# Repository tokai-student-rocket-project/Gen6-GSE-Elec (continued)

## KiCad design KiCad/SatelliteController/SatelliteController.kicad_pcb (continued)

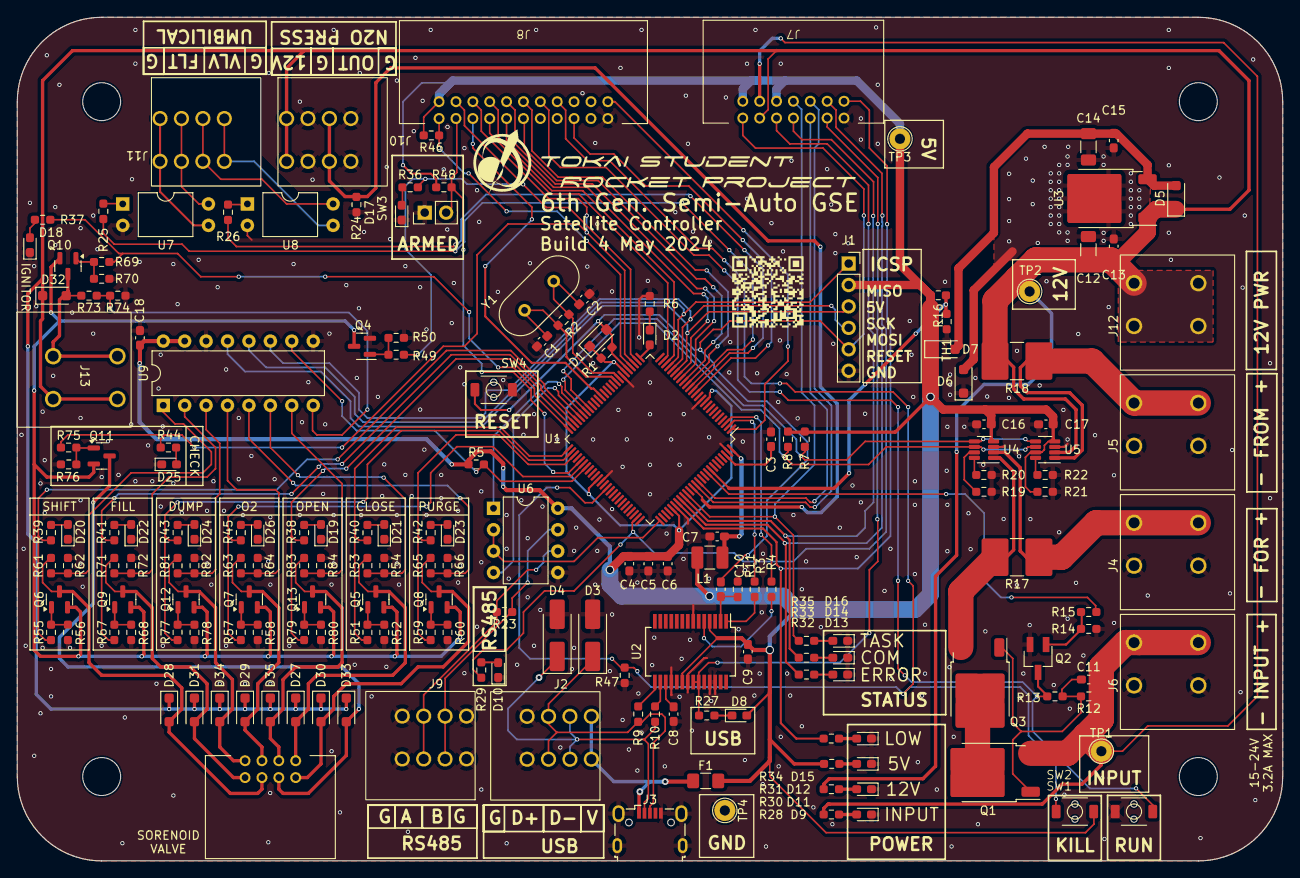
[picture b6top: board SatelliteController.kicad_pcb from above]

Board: 2 copper layers, 150.0 x 100.0 mm, 185 parts (0 on the bottom side), 133 nets.

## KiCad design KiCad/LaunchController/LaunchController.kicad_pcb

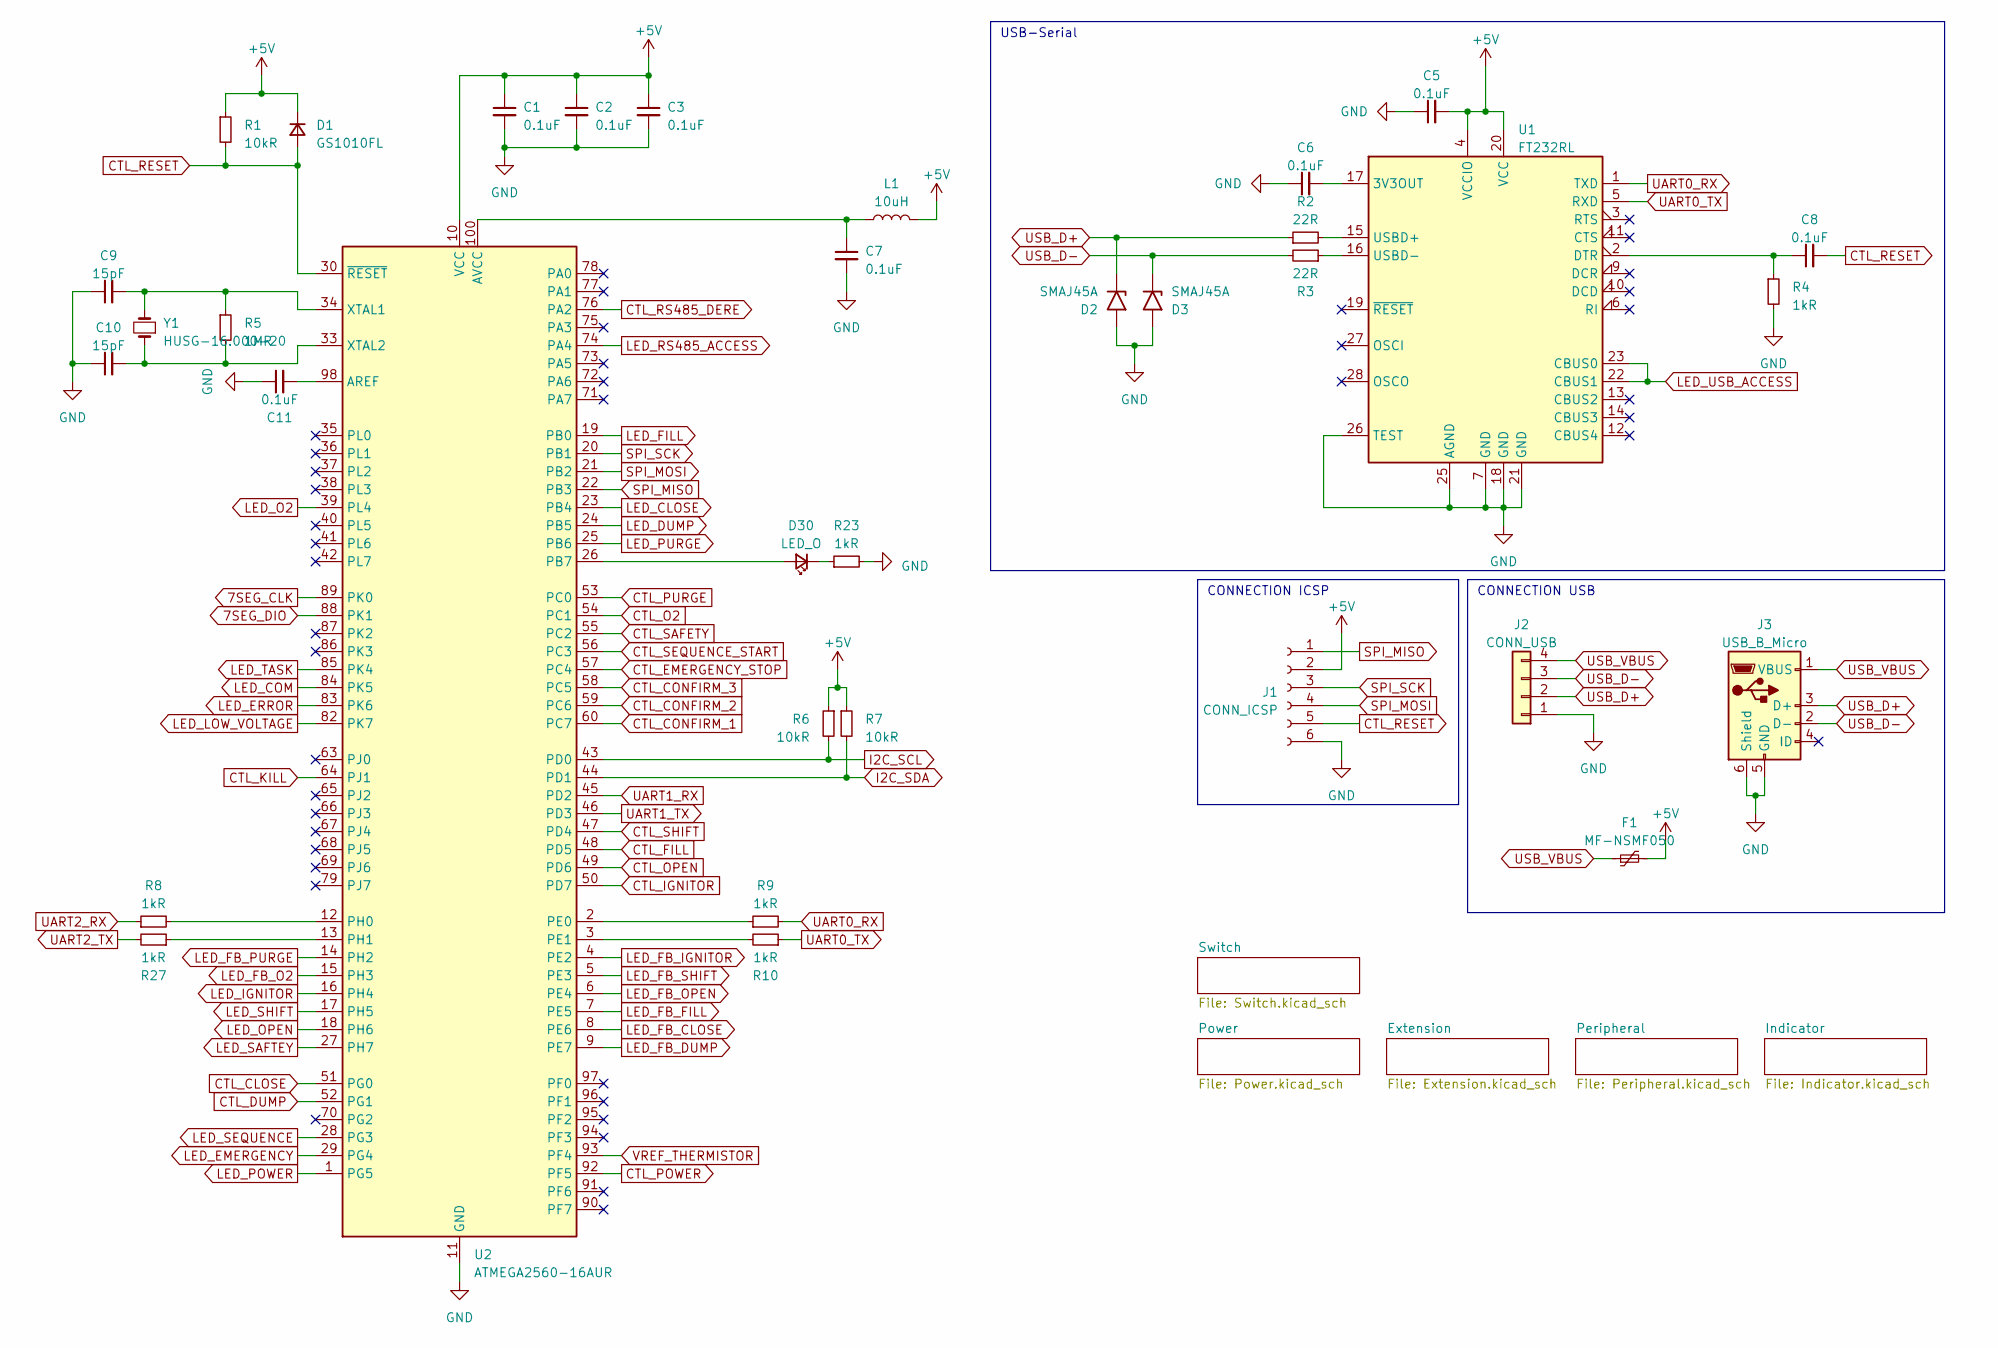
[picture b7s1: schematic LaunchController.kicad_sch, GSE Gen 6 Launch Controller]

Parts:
C1, C2, C3, C5, C6, C7, C8, C11: 0.1uF; C_0603_1608Metric_Pad1.08x0.95mm_HandSolder
C9, C10: 15pF; C_0603_1608Metric_Pad1.08x0.95mm_HandSolder
D1: GS1010FL; D_SOD-123F
D2, D3: SMAJ45A; D_SMA_Handsoldering
D30: LED_O; LED_0603_1608Metric_Pad1.05x0.95mm_HandSolder
F1: MF-NSMF050; Fuse_1206_3216Metric_Pad1.42x1.75mm_HandSolder
J1: CONN_ICSP; PinSocket_1x06_P2.54mm_Vertical
J2: CONN_USB; TB401-1-4-E
J3: USB_B_Micro; USB_Micro-B_Wuerth_629105150521
L1: 10uH; L_1210_3225Metric_Pad1.42x2.65mm_HandSolder
R1, R6, R7: 10kR; R_0603_1608Metric_Pad0.98x0.95mm_HandSolder
R2, R3: 22R; R_0603_1608Metric_Pad0.98x0.95mm_HandSolder
R4, R8, R9, R10, R23, R27: 1kR; R_0603_1608Metric_Pad0.98x0.95mm_HandSolder
R5: 1MR; R_0603_1608Metric_Pad0.98x0.95mm_HandSolder
U1: FT232RL; SSOP-28_5.3x10.2mm_P0.65mm
U2: ATMEGA2560-16AUR; TQFP-100_14x14mm_P0.5mm
Y1: HUSG-16.000-20; Crystal_HC49-U_Vertical

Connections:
7SEG_CLK: U2.89 (PK0); also elsewhere on the board
7SEG_DIO: U2.88 (PK1); also elsewhere on the board
CONN_LED_5V: C1.1, C2.1, C3.1, C5.2, D1.1 (K), F1.2, J1.2, L1.2, R1.1, R6.1, R7.1, U1.4 (VCCIO), U1.20 (VCC), U2.10 (VCC), U2.31 (VCC), U2.61 (VCC), U2.80 (VCC); also elsewhere on the board
CONN_LED_CLOSE: U2.23 (PB4); also elsewhere on the board
CONN_LED_COM: U2.84 (PK5); also elsewhere on the board
CONN_LED_DUMP: U2.24 (PB5); also elsewhere on the board
CONN_LED_EMERGENCY: U2.29 (PG4); also elsewhere on the board
CONN_LED_ERROR: U2.83 (PK6); also elsewhere on the board
CONN_LED_FILL: U2.19 (PB0); also elsewhere on the board
CONN_LED_IGNITOR: U2.16 (PH4); also elsewhere on the board
CONN_LED_LOW_VOLTAGE: U2.82 (PK7); also elsewhere on the board
CONN_LED_O2: U2.39 (PL4); also elsewhere on the board
CONN_LED_OPEN: U2.18 (PH6); also elsewhere on the board
CONN_LED_PURGE: U2.25 (PB6); also elsewhere on the board
CONN_LED_RS485_ACCESS: U2.74 (PA4); also elsewhere on the board
CONN_LED_SAFTEY: U2.27 (PH7); also elsewhere on the board
CONN_LED_SEQUENCE: U2.28 (PG3); also elsewhere on the board
CONN_LED_SHIFT: U2.17 (PH5); also elsewhere on the board
CONN_LED_TASK: U2.85 (PK4); also elsewhere on the board
CONN_LED_USB_ACCESS: U1.22 (CBUS1), U1.23 (CBUS0); also elsewhere on the board
CTL_CLOSE: U2.51 (PG0); also elsewhere on the board
CTL_CONFIRM_1: U2.60 (PC7); also elsewhere on the board
CTL_CONFIRM_2: U2.59 (PC6); also elsewhere on the board
CTL_CONFIRM_3: U2.58 (PC5); also elsewhere on the board
CTL_DUMP: U2.52 (PG1); also elsewhere on the board
CTL_EMERGENCY_STOP: U2.57 (PC4); also elsewhere on the board
CTL_FILL: U2.48 (PD5); also elsewhere on the board
CTL_IGNITOR: U2.50 (PD7); also elsewhere on the board
CTL_KILL: U2.64 (PJ1); also elsewhere on the board
CTL_O2: U2.54 (PC1); also elsewhere on the board
CTL_OPEN: U2.49 (PD6); also elsewhere on the board
CTL_POWER: U2.92 (PF5); also elsewhere on the board
CTL_PURGE: U2.53 (PC0); also elsewhere on the board
CTL_RESET: C8.2, D1.2 (A), J1.5, R1.2, U2.30 (~RESET); also elsewhere on the board
CTL_RS485_DERE: U2.76 (PA2); also elsewhere on the board
CTL_SAFETY: U2.55 (PC2); also elsewhere on the board
CTL_SEQUENCE_START: U2.56 (PC3); also elsewhere on the board
CTL_SHIFT: U2.47 (PD4); also elsewhere on the board
GND: C1.2, C2.2, C3.2, C5.1, C6.1, C7.2, C9.1, C10.1, C11.1, D2.2 (A2), D3.2 (A2), J1.6, J2.1, J3.5 (GND), J3.6 (Shield), R4.2, R23.2, U1.7 (GND), U1.18 (GND), U1.21 (GND), U1.25 (AGND), U1.26 (TEST), U2.11 (GND), U2.32 (GND), U2.62 (GND), U2.81 (GND), U2.99 (GND); also elsewhere on the board
I2C_SCL: R6.2, U2.43 (PD0); also elsewhere on the board
I2C_SDA: R7.2, U2.44 (PD1); also elsewhere on the board
unnamed: D30.2 (A), U2.26 (PB7)
unnamed: D30.1 (K), R23.1
unnamed: C6.2, U1.17 (3V3OUT)
unnamed: C8.1, R4.1, U1.2 (DTR)
unnamed: R2.2, U1.15 (USBD+)
unnamed: R3.1, U1.16 (USBD-)
unnamed: C11.2, U2.98 (AREF)
unnamed: C7.1, L1.1, U2.100 (AVCC)
unnamed: R9.1, U2.2 (PE0)
unnamed: R10.2, U2.3 (PE1)
unnamed: R8.2, U2.12 (PH0)
unnamed: R27.1, U2.13 (PH1)
unnamed: C9.2, R5.1, U2.34 (XTAL1), Y1.2
unnamed: C10.2, R5.2, U2.33 (XTAL2), Y1.1
SPI_MISO: J1.1, U2.22 (PB3)
SPI_MOSI: J1.4, U2.21 (PB2)
SPI_SCK: J1.3, U2.20 (PB1)
UART0_RX: R9.2, U1.1 (TXD)
UART0_TX: R10.1, U1.5 (RXD)
UART1_RX: U2.45 (PD2); also elsewhere on the board
UART1_TX: U2.46 (PD3); also elsewhere on the board
UART2_RX: R8.1; also elsewhere on the board
UART2_TX: R27.2; also elsewhere on the board
USB_D+: D2.1 (A1), J2.2, J3.3 (D+), R2.1
USB_D-: D3.1 (A1), J2.3, J3.2 (D-), R3.2
USB_VBUS: F1.1, J2.4, J3.1 (VBUS)
VREF_THERMISTOR: U2.93 (PF4); also elsewhere on the board

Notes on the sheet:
CONNECTION ICSP
CONNECTION USB
USB-Serial

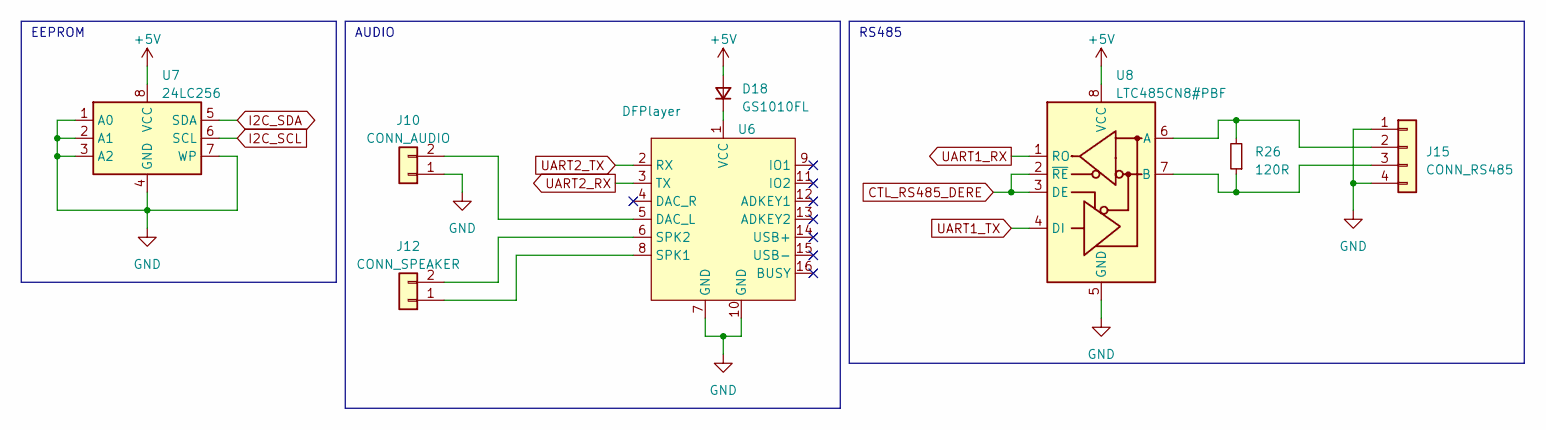
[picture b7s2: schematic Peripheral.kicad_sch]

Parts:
D18: GS1010FL; D_SOD-123F
J10: CONN_AUDIO; TB401-1-2-E
J12: CONN_SPEAKER; TB401-1-2-E
J15: CONN_RS485; TB401-1-4-E
R26: 120R; R_0603_1608Metric_Pad0.98x0.95mm_HandSolder
U6: DFPlayer; DFPlayer-mini
U7: 24LC256; DIP-8_W7.62mm
U8: LTC485CN8#PBF; DIP-8_W7.62mm

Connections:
CONN_LED_5V: D18.2 (A), U7.8 (VCC), U8.8 (VCC); also elsewhere on the board
CTL_RS485_DERE: U8.2 (~RE), U8.3 (DE); also elsewhere on the board
GND: J10.1, J15.1, J15.4, U6.7 (GND), U6.10 (GND), U7.1 (A0), U7.2 (A1), U7.3 (A2), U7.4 (GND), U7.7 (WP), U8.5 (GND); also elsewhere on the board
I2C_SCL: U7.6 (SCL); also elsewhere on the board
I2C_SDA: U7.5 (SDA); also elsewhere on the board
unnamed: D18.1 (K), U6.1 (VCC)
unnamed: J10.2, U6.5 (DAC_L)
unnamed: J12.1, U6.8 (SPK1)
unnamed: J12.2, U6.6 (SPK2)
unnamed: J15.2, R26.2, U8.6 (A)
unnamed: J15.3, R26.1, U8.7 (B)
UART1_RX: U8.1 (RO); also elsewhere on the board
UART1_TX: U8.4 (DI); also elsewhere on the board
UART2_RX: U6.3 (TX); also elsewhere on the board
UART2_TX: U6.2 (RX); also elsewhere on the board

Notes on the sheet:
AUDIO
EEPROM
RS485

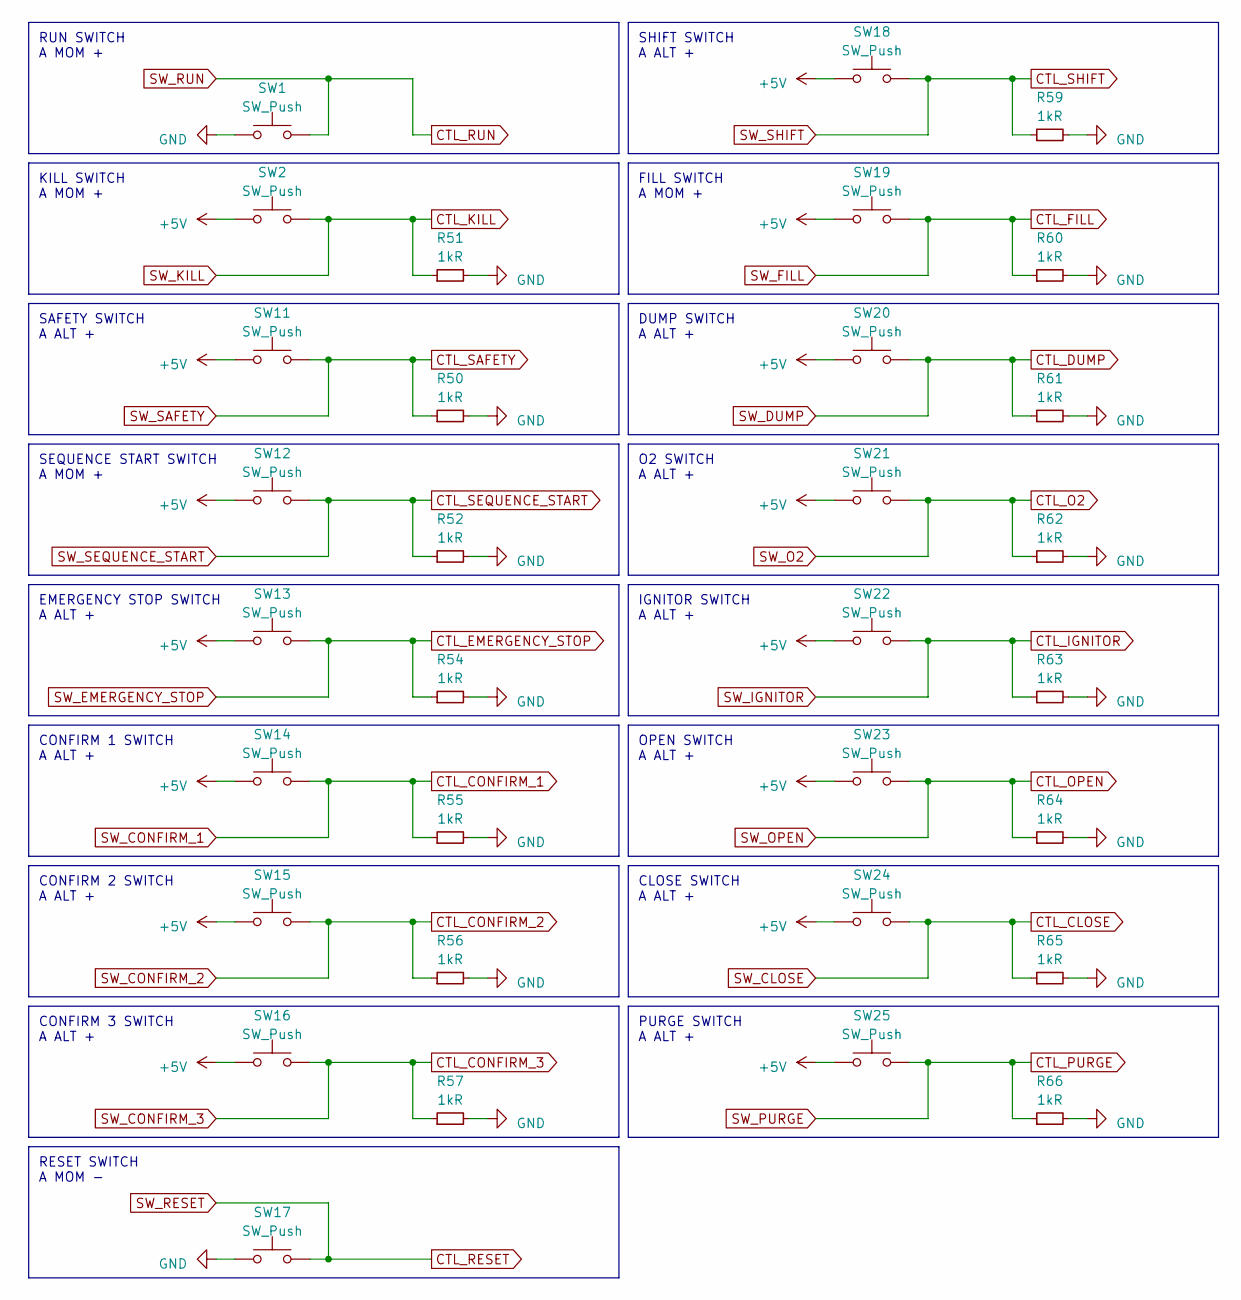
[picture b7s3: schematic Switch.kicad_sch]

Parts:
R50, R51, R52, R54, R55, R56, R57, R59, R60, R61, R62, R63, R64, R65, R66: 1kR; R_0603_1608Metric_Pad0.98x0.95mm_HandSolder
SW1, SW2, SW17: SW_Push; TVAF06-A020B-R
SW11, SW12, SW13, SW14, SW15, SW16, SW18, SW19, SW20, SW21, SW22, SW23, SW24, SW25: SW_Push; PinHeader_1x02_P2.54mm_Vertical

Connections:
CONN_LED_5V: SW2.1, SW11.1, SW12.1, SW13.1, SW14.1, SW15.1, SW16.1, SW18.1, SW19.1, SW20.1, SW21.1, SW22.1, SW23.1, SW24.1, SW25.1; also elsewhere on the board
CTL_CLOSE: R65.1, SW24.2; also elsewhere on the board
CTL_CONFIRM_1: R55.1, SW14.2; also elsewhere on the board
CTL_CONFIRM_2: R56.1, SW15.2; also elsewhere on the board
CTL_CONFIRM_3: R57.1, SW16.2; also elsewhere on the board
CTL_DUMP: R61.1, SW20.2; also elsewhere on the board
CTL_EMERGENCY_STOP: R54.1, SW13.2; also elsewhere on the board
CTL_FILL: R60.1, SW19.2; also elsewhere on the board
CTL_IGNITOR: R63.1, SW22.2; also elsewhere on the board
CTL_KILL: R51.1, SW2.2; also elsewhere on the board
CTL_O2: R62.1, SW21.2; also elsewhere on the board
CTL_OPEN: R64.1, SW23.2; also elsewhere on the board
CTL_PURGE: R66.1, SW25.2; also elsewhere on the board
CTL_RESET: SW17.2; also elsewhere on the board
CTL_RUN: SW1.2; also elsewhere on the board
CTL_SAFETY: R50.1, SW11.2; also elsewhere on the board
CTL_SEQUENCE_START: R52.1, SW12.2; also elsewhere on the board
CTL_SHIFT: R59.1, SW18.2; also elsewhere on the board
GND: R50.2, R51.2, R52.2, R54.2, R55.2, R56.2, R57.2, R59.2, R60.2, R61.2, R62.2, R63.2, R64.2, R65.2, R66.2, SW1.1, SW17.1; also elsewhere on the board

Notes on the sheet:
SEQUENCE START SWITCH A MOM +
OPEN SWITCH A ALT +
CONFIRM 1 SWITCH A ALT +
IGNITOR SWITCH A ALT +
KILL SWITCH A MOM +
CLOSE SWITCH A ALT +
CONFIRM 2 SWITCH A ALT +
SAFETY SWITCH A ALT +
PURGE SWITCH A ALT +
CONFIRM 3 SWITCH A ALT +
SHIFT SWITCH A ALT +
RESET SWITCH A MOM -
FILL SWITCH A MOM +
RUN SWITCH A MOM +
DUMP SWITCH A ALT +
EMERGENCY STOP SWITCH A ALT +
O2 SWITCH A ALT +

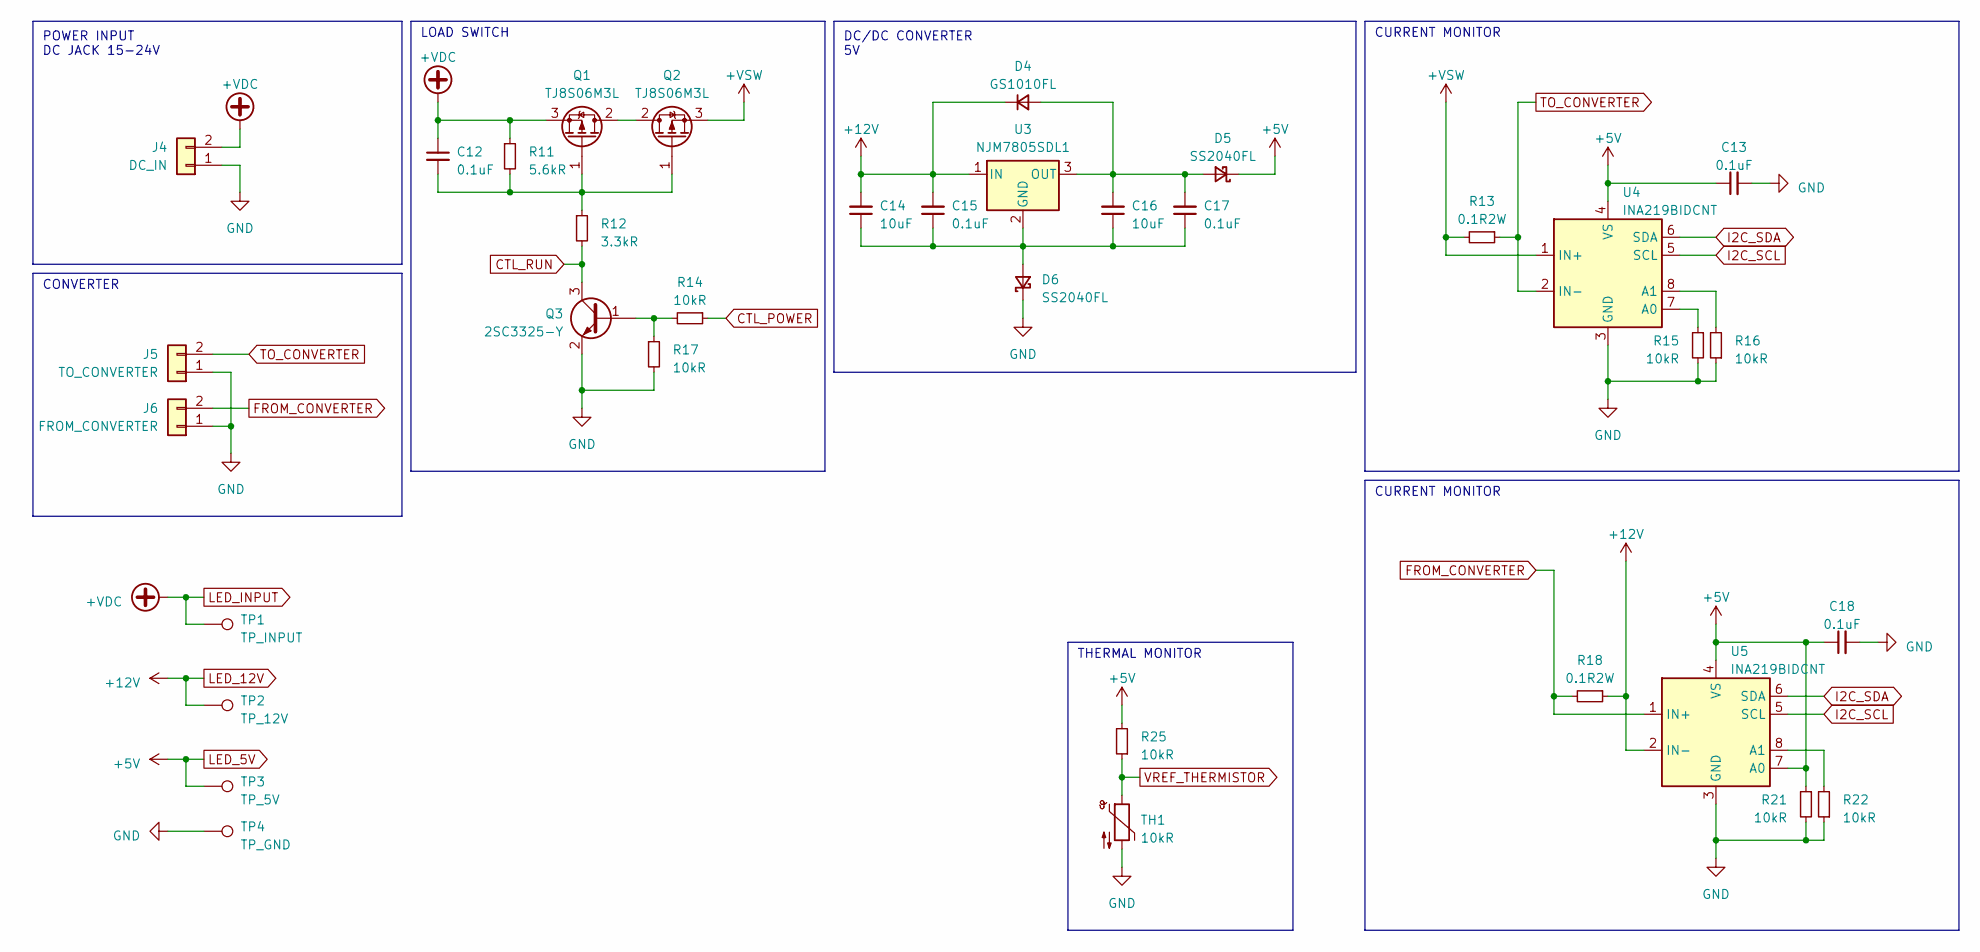
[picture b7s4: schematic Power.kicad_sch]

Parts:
C12, C13, C15, C17, C18: 0.1uF; C_0603_1608Metric_Pad1.08x0.95mm_HandSolder
C14, C16: 10uF; C_1206_3216Metric_Pad1.33x1.80mm_HandSolder
D4: GS1010FL; D_SOD-123F
D5, D6: SS2040FL; D_SOD-123F
J4: DC_IN; TB411-2-2-E-1
J5: TO_CONVERTER; TB411-2-2-E-1
J6: FROM_CONVERTER; TB411-2-2-E-1
Q1, Q2: TJ8S06M3L; TO-252-2
Q3: 2SC3325-Y; SC-59_Handsoldering
R11: 5.6kR; R_0603_1608Metric_Pad0.98x0.95mm_HandSolder
R12: 3.3kR; R_0603_1608Metric_Pad0.98x0.95mm_HandSolder
R13, R18: 0.1R2W; R_2816_7142Metric_Pad3.20x4.45mm_HandSolder
R14, R15, R16, R17, R21, R22, R25: 10kR; R_0603_1608Metric_Pad0.98x0.95mm_HandSolder
TH1: 10kR; R_0603_1608Metric_Pad0.98x0.95mm_HandSolder
TP1: TP_INPUT; TestPoint_THTPad_D2.5mm_Drill1.2mm
TP2: TP_12V; TestPoint_THTPad_D2.5mm_Drill1.2mm
TP3: TP_5V; TestPoint_THTPad_D2.5mm_Drill1.2mm
TP4: TP_GND; TestPoint_THTPad_D2.5mm_Drill1.2mm
U3: NJM7805SDL1; TO-252-2
U4, U5: INA219BIDCNT; SOT-23-8

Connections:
+VSW: Q2.3 (S), R13.2, U4.1 (IN+)
CONN_LED_5V: C13.1, C18.1, D5.1 (K), R21.1, R25.2, TP3.1, U4.4 (VS), U5.4 (VS), U5.7 (A0); also elsewhere on the board
CONN_LED_12V: C14.2, C15.2, D4.1 (K), R18.1, TP2.1, U3.1 (IN), U5.2 (IN-); also elsewhere on the board
CONN_LED_INPUT: C12.1, J4.2, Q1.3 (S), R11.1, TP1.1; also elsewhere on the board
CTL_POWER: R14.1; also elsewhere on the board
CTL_RUN: Q3.3 (C), R12.2; also elsewhere on the board
FROM_CONVERTER: J6.2, R18.2, U5.1 (IN+)
GND: C13.2, C18.2, D6.1 (K), J4.1, J5.1, J6.1, Q3.2 (E), R15.2, R16.1, R17.2, R21.2, R22.1, TH1.2, TP4.1, U4.3 (GND), U5.3 (GND); also elsewhere on the board
I2C_SCL: U4.5 (SCL), U5.5 (SCL); also elsewhere on the board
I2C_SDA: U4.6 (SDA), U5.6 (SDA); also elsewhere on the board
unnamed: C16.2, C17.2, D4.2 (A), D5.2 (A), U3.3 (OUT)
unnamed: C14.1, C15.1, C16.1, C17.1, D6.2 (A), U3.2 (GND)
unnamed: Q1.2 (D), Q2.2 (D)
unnamed: C12.2, Q1.1 (G), Q2.1 (G), R11.2, R12.1
unnamed: Q3.1 (B), R14.2, R17.1
unnamed: R15.1, U4.7 (A0)
unnamed: R16.2, U4.8 (A1)
unnamed: R22.2, U5.8 (A1)
TO_CONVERTER: J5.2, R13.1, U4.2 (IN-)
VREF_THERMISTOR: R25.1, TH1.1; also elsewhere on the board

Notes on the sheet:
CURRENT MONITOR
POWER INPUT DC JACK 15-24V
DC/DC CONVERTER 5V
CONVERTER
THERMAL MONITOR
LOAD SWITCH

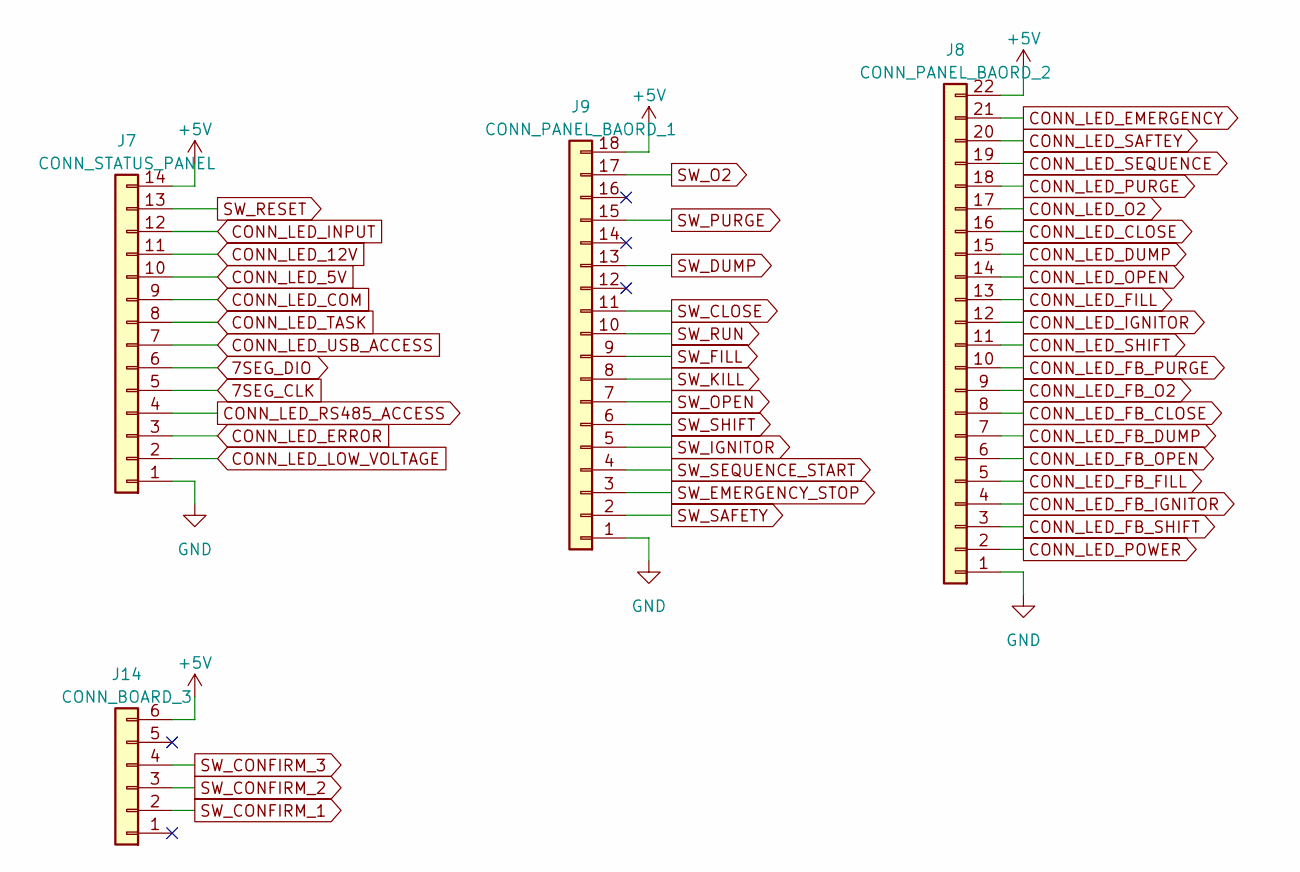
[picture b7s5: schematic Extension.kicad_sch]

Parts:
J7: CONN_STATUS_PANEL; DF51A-14DP-2DS
J8: CONN_PANEL_BAORD_2; DF51A-22DP-2DS
J9: CONN_PANEL_BAORD_1; DF51A-18DP-2DS
J14: CONN_BOARD_3; DF51A-6DP-2DSA

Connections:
7SEG_CLK: J7.5; also elsewhere on the board
7SEG_DIO: J7.6; also elsewhere on the board
CONN_LED_5V: J7.10, J7.14, J8.22, J9.18, J14.6; also elsewhere on the board
CONN_LED_12V: J7.11; also elsewhere on the board
CONN_LED_CLOSE: J8.16; also elsewhere on the board
CONN_LED_COM: J7.9; also elsewhere on the board
CONN_LED_DUMP: J8.15; also elsewhere on the board
CONN_LED_EMERGENCY: J8.21; also elsewhere on the board
CONN_LED_ERROR: J7.3; also elsewhere on the board
CONN_LED_FILL: J8.13; also elsewhere on the board
CONN_LED_IGNITOR: J8.12; also elsewhere on the board
CONN_LED_INPUT: J7.12; also elsewhere on the board
CONN_LED_LOW_VOLTAGE: J7.2; also elsewhere on the board
CONN_LED_O2: J8.17; also elsewhere on the board
CONN_LED_OPEN: J8.14; also elsewhere on the board
CONN_LED_PURGE: J8.18; also elsewhere on the board
CONN_LED_RS485_ACCESS: J7.4; also elsewhere on the board
CONN_LED_SAFTEY: J8.20; also elsewhere on the board
CONN_LED_SEQUENCE: J8.19; also elsewhere on the board
CONN_LED_SHIFT: J8.11; also elsewhere on the board
CONN_LED_TASK: J7.8; also elsewhere on the board
CONN_LED_USB_ACCESS: J7.7; also elsewhere on the board
CTL_CLOSE: J9.11; also elsewhere on the board
CTL_CONFIRM_1: J14.2; also elsewhere on the board
CTL_CONFIRM_2: J14.3; also elsewhere on the board
CTL_CONFIRM_3: J14.4; also elsewhere on the board
CTL_DUMP: J9.13; also elsewhere on the board
CTL_EMERGENCY_STOP: J9.3; also elsewhere on the board
CTL_FILL: J9.9; also elsewhere on the board
CTL_IGNITOR: J9.5; also elsewhere on the board
CTL_KILL: J9.8; also elsewhere on the board
CTL_O2: J9.17; also elsewhere on the board
CTL_OPEN: J9.7; also elsewhere on the board
CTL_PURGE: J9.15; also elsewhere on the board
CTL_RESET: J7.13; also elsewhere on the board
CTL_RUN: J9.10; also elsewhere on the board
CTL_SAFETY: J9.2; also elsewhere on the board
CTL_SEQUENCE_START: J9.4; also elsewhere on the board
CTL_SHIFT: J9.6; also elsewhere on the board
GND: J7.1, J8.1, J9.1; also elsewhere on the board

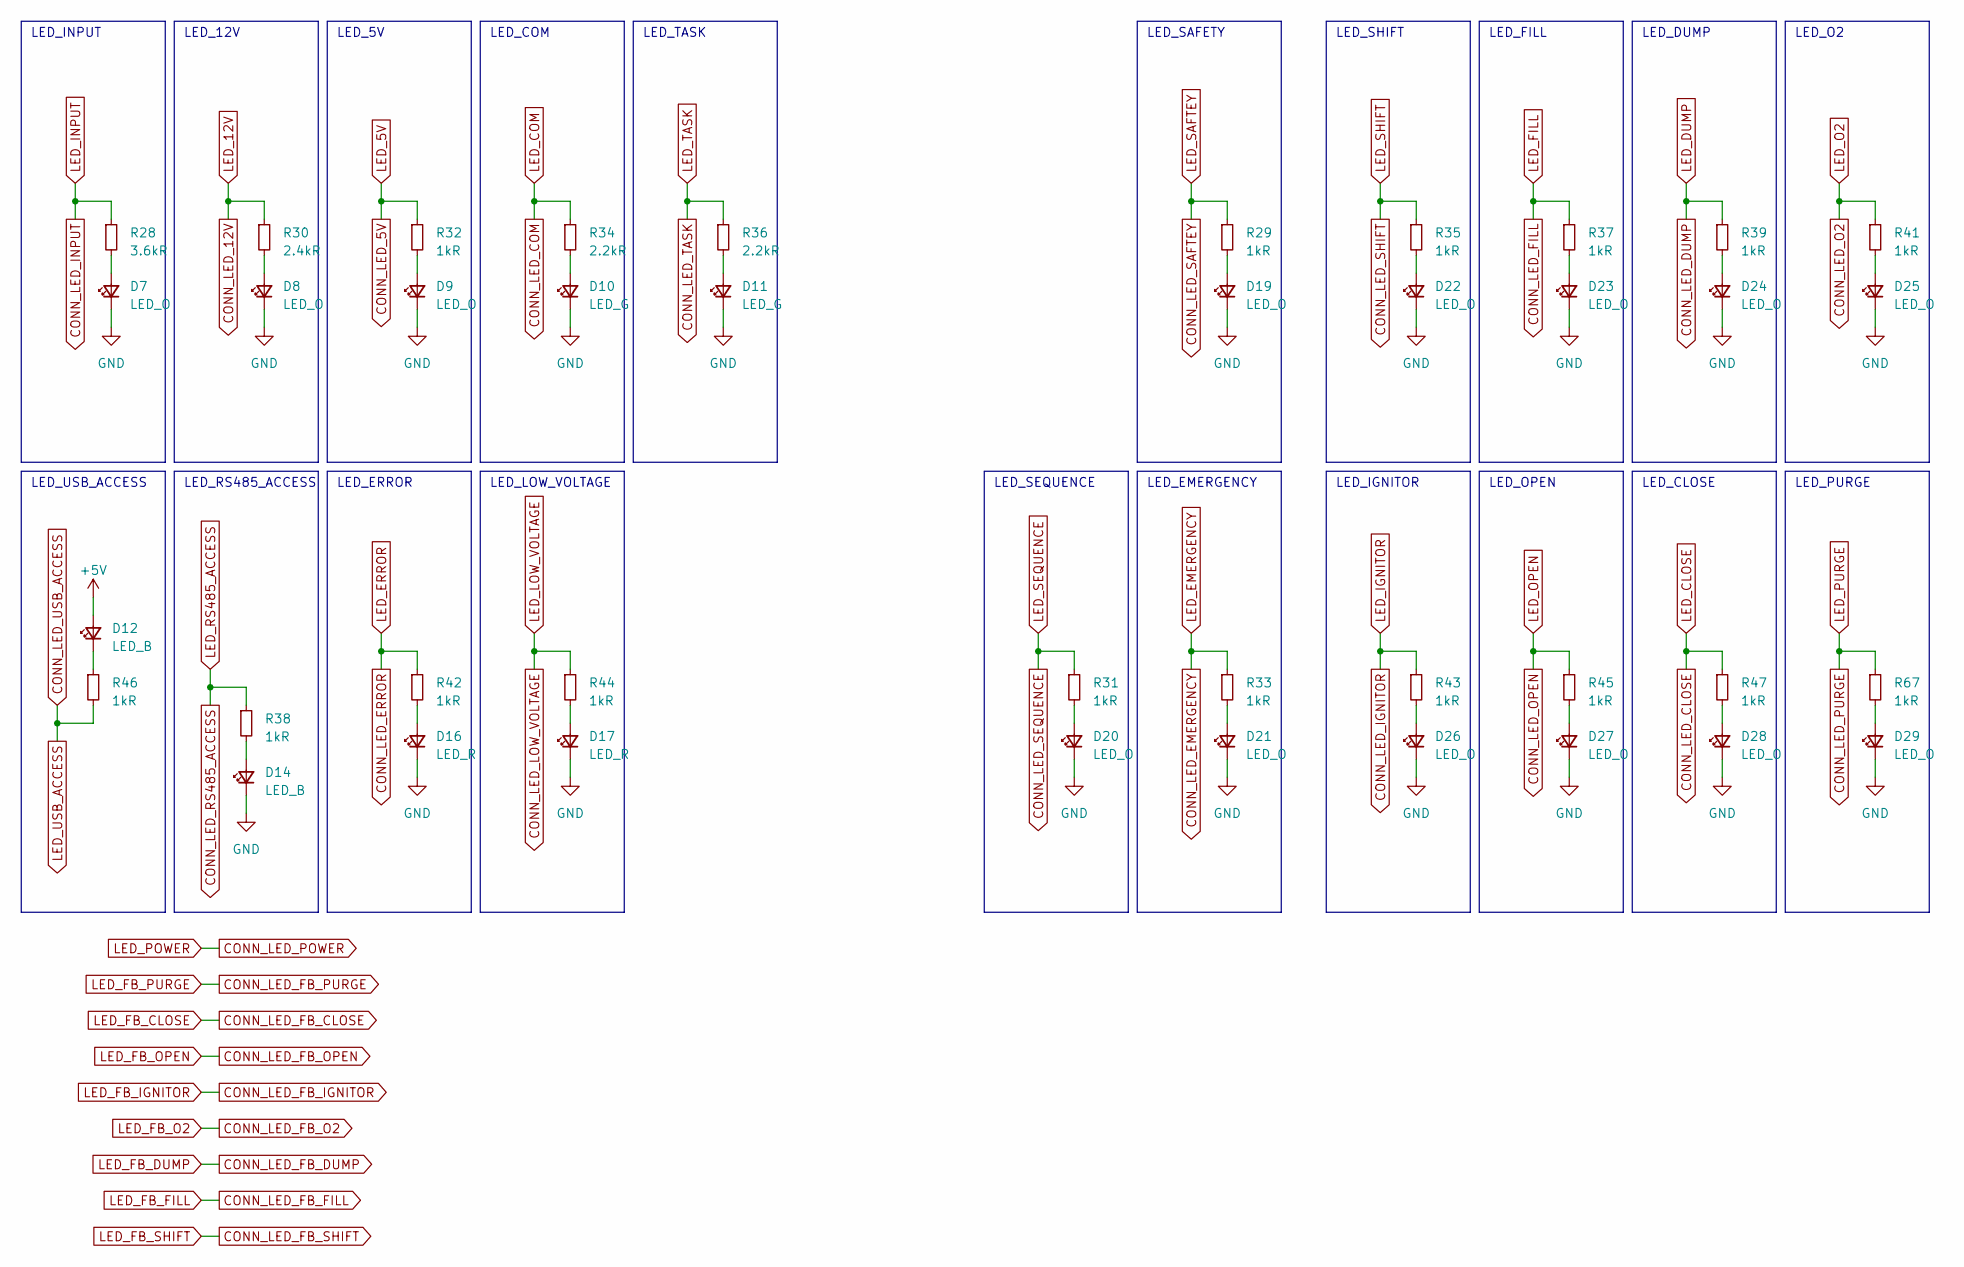
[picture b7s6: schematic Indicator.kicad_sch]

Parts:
D7, D8, D9, D19, D20, D21, D22, D23, D24, D25, D26, D27, D28, D29: LED_O; LED_0603_1608Metric_Pad1.05x0.95mm_HandSolder
D10, D11: LED_G; LED_0603_1608Metric_Pad1.05x0.95mm_HandSolder
D12, D14: LED_B; LED_0603_1608Metric_Pad1.05x0.95mm_HandSolder
D16, D17: LED_R; LED_0603_1608Metric_Pad1.05x0.95mm_HandSolder
R28: 3.6kR; R_0603_1608Metric_Pad0.98x0.95mm_HandSolder
R29, R31, R32, R33, R35, R37, R38, R39, R41, R42, R43, R44, R45, R46, R47, R67: 1kR; R_0603_1608Metric_Pad0.98x0.95mm_HandSolder
R30: 2.4kR; R_0603_1608Metric_Pad0.98x0.95mm_HandSolder
R34, R36: 2.2kR; R_0603_1608Metric_Pad0.98x0.95mm_HandSolder

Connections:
CONN_LED_5V: D12.2 (A), R32.1; also elsewhere on the board
CONN_LED_12V: R30.1; also elsewhere on the board
CONN_LED_CLOSE: R47.1; also elsewhere on the board
CONN_LED_COM: R34.1; also elsewhere on the board
CONN_LED_DUMP: R39.1; also elsewhere on the board
CONN_LED_EMERGENCY: R33.1; also elsewhere on the board
CONN_LED_ERROR: R42.1; also elsewhere on the board
CONN_LED_FILL: R37.1; also elsewhere on the board
CONN_LED_IGNITOR: R43.1; also elsewhere on the board
CONN_LED_INPUT: R28.1; also elsewhere on the board
CONN_LED_LOW_VOLTAGE: R44.1; also elsewhere on the board
CONN_LED_O2: R41.1; also elsewhere on the board
CONN_LED_OPEN: R45.1; also elsewhere on the board
CONN_LED_PURGE: R67.1; also elsewhere on the board
CONN_LED_RS485_ACCESS: R38.1; also elsewhere on the board
CONN_LED_SAFTEY: R29.1; also elsewhere on the board
CONN_LED_SEQUENCE: R31.1; also elsewhere on the board
CONN_LED_SHIFT: R35.1; also elsewhere on the board
CONN_LED_TASK: R36.1; also elsewhere on the board
CONN_LED_USB_ACCESS: R46.2; also elsewhere on the board
GND: D7.1 (K), D8.1 (K), D9.1 (K), D10.1 (K), D11.1 (K), D14.1 (K), D16.1 (K), D17.1 (K), D19.1 (K), D20.1 (K), D21.1 (K), D22.1 (K), D23.1 (K), D24.1 (K), D25.1 (K), D26.1 (K), D27.1 (K), D28.1 (K), D29.1 (K); also elsewhere on the board
unnamed: D7.2 (A), R28.2
unnamed: D8.2 (A), R30.2
unnamed: D9.2 (A), R32.2
unnamed: D10.2 (A), R34.2
unnamed: D11.2 (A), R36.2
unnamed: D12.1 (K), R46.1
unnamed: D14.2 (A), R38.2
unnamed: D16.2 (A), R42.2
unnamed: D17.2 (A), R44.2
unnamed: D19.2 (A), R29.2
unnamed: D20.2 (A), R31.2
unnamed: D21.2 (A), R33.2
unnamed: D22.2 (A), R35.2
unnamed: D23.2 (A), R37.2
unnamed: D24.2 (A), R39.2
unnamed: D25.2 (A), R41.2
unnamed: D26.2 (A), R43.2
unnamed: D27.2 (A), R45.2
unnamed: D28.2 (A), R47.2
unnamed: D29.2 (A), R67.2

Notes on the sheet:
LED_SEQUENCE
LED_CLOSE
LED_ERROR
LED_RS485_ACCESS
LED_DUMP
LED_TASK
LED_PURGE
LED_FILL
LED_EMERGENCY
LED_LOW_VOLTAGE
LED_O2
LED_COM
LED_5V
LED_SHIFT
LED_USB_ACCESS
LED_IGNITOR
LED_OPEN
LED_INPUT
LED_SAFETY
LED_12V

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
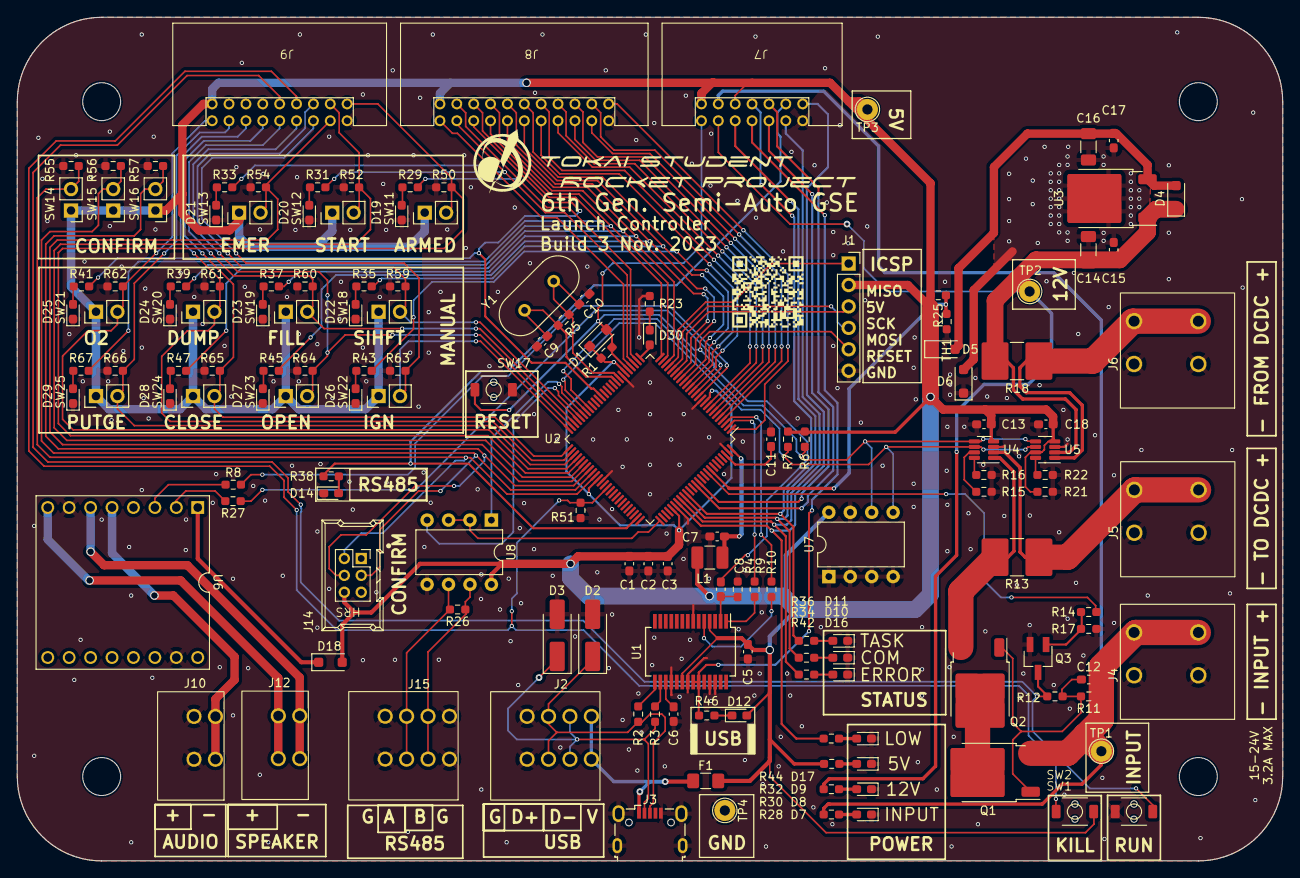
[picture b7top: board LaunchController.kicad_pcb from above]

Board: 2 copper layers, 150.0 x 100.0 mm, 153 parts (0 on the bottom side), 117 nets.
